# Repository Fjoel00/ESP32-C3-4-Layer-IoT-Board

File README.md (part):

# ESP32-C3 4-Layer IoT Multisensor Board 🚀

Nodo IoT embebido multisensor de **4 capas**, compacto y de bajo consumo, basado en el microcontrolador **Espressif ESP32-C3-WROOM-02** (arquitectura RISC-V a 160 MHz con conectividad Wi-Fi 4 y Bluetooth 5 LE). 

El diseño integra una solución completa de gestión de energía con carga de batería LiPo y conmutación automática (*Power-Path Management*), interfaz USB-C nativa con puente USB-UART CP2102N y auto-reset, almacenamiento masivo local dual (Flash SPI externa de 32 Mbit + ranura MicroSD), sensor ambiental de alta precisión (temperatura, presión y humedad), fototransistor de luz ambiental y micrófono electret con etapa de preamplificación activa ajustable.

Este proyecto ha sido concebido bajo estrictas pautas de diseño electrónico profesional, cumpliendo con restricciones de compatibilidad electromagnética (EMC), integridad de señal (SI) para pares diferenciales USB y buses de alta velocidad, optimización térmica y validación DFM (*Design for Manufacturability*) para fabricación seriada.

---

## Render 3D del Hardware y Documentación

* **Esquemático Completo:** [Ver / Descargar Esquemático en PDF](./ESP32-IoT-4-Layer-3D-Layout.pdf)
* **Visualización de PCB 3D:** [Ver / Descargar Vista 3D en PDF](./ESP32-IoT-4-Layer-3D-PCB.pdf)
* **Archivos Gerber y Taladros (NextPCB / HQ DFM):** [Descargar Paquete Gerber ZIP](./HQDMF/Gerber_ESP32-IoT-4-Layer.zip)

---

## Tabla de Contenidos
- [1. Descripción General del Proyecto](#1-descripción-general-del-proyecto)
- [2. Arquitectura de Hardware y Características Principales](#2-arquitectura-de-hardware-y-características-principales)
  - [2.1 Microcontrolador y Conectividad](#21-microcontrolador-y-conectividad)
  - [2.2 Gestión de Energía y Batería (Power-Path Management)](#22-gestión-de-energía-y-batería-power-path-management)
  - [2.3 Sensores Integrados](#23-sensores-integrados)
  - [2.4 Almacenamiento Local y Puntos de Prueba](#24-almacenamiento-local-y-puntos-de-prueba)
  - [2.5 Interfaz de Usuario y Cabezales de Expansión](#25-interfaz-de-usuario-y-cabezales-de-expansión)
- [3. Diseño de PCB y Stackup (4 Capas)](#3-diseño-de-pcb-y-stackup-4-capas)
  - [3.1 Distribución del Stackup y Dimensiones](#31-distribución-del-stackup-y-dimensiones)
  - [3.2 Enrutamiento de Señales Críticas y Pares Diferenciales USB](#32-enrutamiento-de-señales-críticas-y-pares-diferenciales-usb)
  - [3.3 Clases de Red (Net Classes) y Reglas de Diseño](#33-clases-de-red-net-classes-y-reglas-de-diseño)
  - [3.4 Consideraciones de RF y Planos de Cobre](#34-consideraciones-de-rf-y-planos-de-cobre)
- [4. Estructura del Repositorio y Hojas del Esquemático](#4-estructura-del-repositorio-y-hojas-del-esquemático)
- [5. Lista de Materiales (BOM Resumida)](#5-lista-de-materiales-bom-resumida)
- [6. Herramientas y Recursos Utilizados](#6-herramientas-y-recursos-utilizados)
- [7. Créditos y Referencias](#7-créditos-y-referencias)

---

## 1. Descripción General del Proyecto

La placa ha sido desarrollada como una plataforma integral de adquisición de datos en tiempo real y telemetría edge computing. Permite monitorear parámetros ambientales, acústicos y luminosos, procesarlos localmente en el núcleo RISC-V del microcontrolador y transmitirlos a la nube (AWS IoT Core, ThingsBoard, Home Assistant, servidores MQTT) mediante Wi-Fi o Bluetooth LE.

```mermaid
flowchart LR
    USB["Puerto USB-C\n(SS-52400-002)"] --> ESD["Protección ESD\n(USBLC6-2SC6)"]
    ESD --> CP["Puente USB-UART\n(CP2102N)"]
    CP --> AutoReset["Auto-Reset / Boot\n(2x BC817)"]
    AutoReset --> ESP["ESP32-C3-WROOM-02\n(RISC-V 160MHz)"]

    USB --> Fuse["Fusible PPTC 1.1A\n(0ZCH0110AF2E)"]
    Fuse --> MCP["Cargador LiPo + Power Path\n(MCP73871)"]
    BAT["Batería LiPo 3.7V\n(JST-PH 2-pin)"] <--> MCP
    MCP --> LDO["Regulador LDO 3.3V\n(LM1117-3.3)"]
    LDO --> ESP

    ESP <--> BME["Sensor BME280\n(I2C: Temp/Hum/Pres)"]
    ESP <--> TEMT["Sensor TEMT6000\n(ADC: Luz Ambiental)"]
    ESP <--> MIC["Micrófono + MAX4466\n(ADC: Acústica)"]
    ESP <--> Flash["Flash SPI 32 Mbit\n(W25Q32JV)"]
    ESP <--> SD["Ranura MicroSD\n(GSD090012SEU)"]
    ESP <--> EXP["Headers J4 / J5\n(GPIO & OLED I2C)"]
```

---

## 2. Arquitectura de Hardware y Características Principales

### 2.1 Microcontrolador y Conectividad
* **MCU:** Módulo **ESP32-C3-WROOM-02-H4** de Espressif Systems.
  * Núcleo: Procesador RISC-V de 32 bits y un solo núcleo a una frecuencia de hasta 160 MHz.
  * Memoria: 400 KB de SRAM interna, 384 KB de ROM y 4 MB de memoria Flash integrada en encapsulado SiP.
  * Conectividad RF: Subsistema Wi-Fi 802.11 b/g/n (hasta 150 Mbps) y Bluetooth 5 (LE) con antena PCB tipo MIFA integrada.
* **Interfaz USB-C:** Conector hembra reversible **SS-52400-002** (Bel Fuse) de 24 pines con resistencias de configuración de canal CC1/CC2 de 5.1 kΩ (`R3` y `R7`), garantizando compatibilidad con cargadores y puertos USB-C estándar (5 V @ hasta 3 A).
* **Supresión de Transitorios ESD:** Red de diodos de protección **USBLC6-2SC6** (`U2`, encapsulado SOT-23-6) de muy baja capacitancia parásita (<3.5 pF) para proteger las líneas `USB_DP`, `USB_DN` y el riel `VBUS` contra descargas electrostáticas de hasta ±15 kV por aire y ±8 kV por contacto (IEC 61000-4-2 nivel 4).
* **Puente USB a UART:** Circuito integrado **CP2102N-Axx-xQFN20** (`U3`, encapsulado QFN-20 de 3x3 mm) con soporte de velocidades de baudios de hasta 3 Mbaud.
  * Indicadores visuales de actividad de transmisión (`LED5` rojo para `TXT`) y recepción (`LED6` verde para `RXT`).
  * Resistencias de amortiguación en serie de 50 Ω (`R13` y `R17`) en las líneas UART para reducir reflexiones de alta frecuencia.
* **Circuito de Auto-Programación / Auto-Reset:** Implementado mediante dos transistores NPN discretos **BC817** (`Q2` y `Q3`) controlados por las señales `DTR` y `RTS` del CP2102N, permitiendo la conmutación automática entre modo normal y modo de descarga de firmware (control de líneas `EN` y `GPIO9/BOOT`) sin requerir pulsación manual de botones durante el flasheo desde el ESP-IDF o PlatformIO.

### 2.2 Gestión de Energía y Batería (Power-Path Management)
* **Controlador de Carga LiPo:** Circuito integrado **MCP73871-4CCI/ML** (`U1`, QFN-20 de 4x4 mm con pad térmico expuesto).
  * Algoritmo de carga completo en corriente constante / tensión constante (CC/CV) con corte a 4.20 V.
  * **Power-Path Management Automático:** Conmuta de forma transparente el riel del sistema entre la entrada de alimentación externa (USB de 5 V) y la batería LiPo. Si la corriente de carga y consumo supera el límite provisto por USB, la batería asiste automáticamente al riel del sistema sin reiniciar el microcontrolador.
  * Monitoreo térmico mediante red resistiva simulando termistor NTC (`Net-(U1-THERM)`).
* **Conexión de Batería:** Conector de montaje superficial **JST B2B-PH-SM4-TB** (`J2`) con paso de 2.0 mm para baterías de polímero de litio (LiPo) de una celda (1S, 3.7 V nominal).
* **Protección de Entrada:** Fusible rearmable de coeficiente de temperatura positivo polimérico (PPTC) **0ZCH0110AF2E** (`F1`, tamaño 1210), con corriente de mantenimiento ($I_H$) de 1.10 A y tensión nominal de 16 V, protegiendo el hardware ante sobrecorrientes en el bus USB.
* **Regulación a 3.3 V:** Regulador lineal LDO de bajo dropout **LM1117MPX-3.3/NOPB** (`VR1`, encapsulado SOT-223) capaz de suministrar hasta 800 mA con excelente rechazo al rizado (PSRR).
  * Red de filtrado con condensadores de tantalio de baja ESR **10 µF** (`C4`, `C5`, `C12`, `C13`, encapsulado EIA 3216 / KEMET T491A) y cerámicos multicapa (MLCC) de desacoplo de alta frecuencia de **0.1 µF** y **1 µF**.
* **LEDs de Diagnóstico y Estado:**
  * `LED1` (Rojo): Indicador de batería en proceso de carga (`/CHARGING`, pin `STAT1`).
  * `LED2` (Azul): Indicador de fuente de alimentación válida presente (`/CHARGING_POWER_GOOD`, pin `/PG`).
  * `LED3` (Verde): Indicador de ciclo de carga completado (`/CHARGED`, pin `STAT2`).
  * `LED4` (Rojo): Indicador de riel de alimentación principal activo (+3.3V Power Good).

### 2.3 Sensores Integrados
* **Sensor Ambiental Multivariable (U6 - BME280):**
  * Fabricante: Bosch Sensortec (encapsulado LGA-8 metálico de 2.5 x 2.5 mm).
  * Mide simultáneamente temperatura ambiente (precisión ±0.5 °C), humedad relativa (precisión ±3 %) y presión barométrica (precisión ±1 hPa, permitiendo cálculo de altitud barométrica).
  * Interfaz de comunicación: Bus I2C conectado a las líneas `SDA` (`GPIO4`) y `SCL` (`GPIO5`) del ESP32-C3, con resistencias pull-up de 4.7 kΩ (`R21` y `R24`).
* **Sensor de Luz Ambiental (Q1 - TEMT6000X01):**
  * Fabricante: Vishay Semiconductors (encapsulado SMD 1206 transparente).
  * Fototransistor NPN de silicio epitaxial planar con sensibilidad espectral adaptada a la respuesta fotópica del ojo humano (longitud de onda pico $\lambda_p = 570\text{ nm}$).
  * Configuración en emisor común con resistencia de carga a tierra, entregando una señal analógica proporcional a la iluminancia (Lux) hacia el canal ADC `PHOTO_C` (`GPIO1` / Pin 17 del ESP32-C3).
* **Sensor Acústico y Preamplificador de Micrófono (MK1 + U7):**
  * **Micrófono:** Transductor de condensador electret omnidireccional **CMC-5042PF-AC** (`MK1`, CUI Devices, 5.0 mm de diámetro) con rango de frecuencia de 100 Hz a 20 kHz y relación señal/ruido (SNR) >58 dB.
  * **Preamplificador:** Amplificador operacional **MAX4466EXK** (`U7`, Maxim Integrated / Analog Devices en encapsulado SC-70-5) con ancho de banda de 600 kHz y salida rail-to-rail.
  * Integra polarización activa para el micrófono, acoplamiento AC mediante condensadores de 1 µF y 10 nF (`C21`, `C22`), y red de realimentación para control de ganancia dinámica entregando la señal acondicionada `MIC_OUT` (`GPIO0` / Pin 4 del ESP32-C3) para detección de audio, decibelímetro o análisis FFT.

### 2.4 Almacenamiento Local y Puntos de Prueba
* **Memoria Flash SPI Externa (U4 - W25Q32JVSSIQ):**
  * Memoria NOR Flash serial de **32 Mbit (4 MByte)** en encapsulado SOIC-8 (208 mil).
  * Conectada al bus SPI compartido (`SCLK`, `MOSI_DI`, `MISO_DO`) con línea de selección dedicada `CS` (`GPIO10`).
  * Resistencias de amortiguación en serie de 50 Ω (`R18`, `R19`, `R20`) para evitar rebotes capacitivos e interferencias inductivas a altas frecuencias de reloj (hasta 133 MHz).
* **Ranura para Tarjeta MicroSD (J3 - GSD090012SEU):**
  * Conector push-push/push-pull de montaje superficial de Amphenol ICC.
  * Opera en modo SPI utilizando la línea de selección de chip dedicada `CS_SD` (`GPIO3`).
  * Permite registro continuo de datos (*datalogging*) masivo, almacenamiento de certificados criptográficos SSL/TLS, configuración JSON o recursos multimedia web locales.
* **Puntos de Prueba (Test Points):**
  * Cinco pads circulares de 1.0 mm de diámetro accesibles en la cara superior para conexión directa de analizadores lógicos o sondas de osciloscopio:
    * `TP1`: Bus SPI - MOSI
    * `TP2`: Bus SPI - MISO
    * `TP3`: Bus SPI - SCLK
    * `TP4`: Chip Select MicroSD (`CS_SD`)
    * `TP5`: Chip Select Flash SPI (`CS`)

### 2.5 Interfaz de Usuario y Cabezales de Expansión
* **Pulsadores Físicos de Perfil Bajo:**
  * `S1` (`BOOT`): Pulsador táctil SMD de precisión (`SW_USLPT2819DT2TR`, TE Connectivity) conectado a `GPIO9` con filtro capacitivo de 1 µF (`C20`) y resistencia pull-up de 10 kΩ (`R31`).
  * `S2` (`RESET`): Pulsador táctil idéntico conectado a la línea de habilitación `EN` con condensador de temporización de 0.1 µF (`C19`) y pull-up de 10 kΩ (`R30`).
* **Conector de Expansión I2C / Pantalla OLED (J5):**
  * Header hembra/macho estándar paso 2.54 mm de 4 pines con el pinout canónico para módulos display OLED SSD1306 (0.96 pulgada, 128x64 píxeles):
    * **Pin 1:** `+3.3V` (Alimentación regulada)
    * **Pin 2:** `SDA` (Línea de datos I2C)
    * **Pin 3:** `SCL` (Línea de reloj I2C)
    * **Pin 4:** `GND` (Referencia común de masa)
* **Conector de Expansión de GPIOs Multipropósito (J4):**
  * Header paso 2.54 mm de 5 pines para conectar actuadores externos, relés o periféricos SPI adicionales:
    * **Pin 1:** `+3.3V`
    * **Pin 2:** `GPIO8` (Línea digital de entrada/salida)
    * **Pin 3:** `GPIO18` (Línea digital de entrada/salida)
    * **Pin 4:** `GPIO19` (Línea digital de entrada/salida)
    * **Pin 5:** `GND`

---

## 3. Diseño de PCB y Stackup (4 Capas)

La placa utiliza una arquitectura multicapa de **4 estratos de cobre** con espesor final estándar de 1.6 mm y material dieléctrico FR-4 ($\varepsilon_r = 4.5, \tan\delta = 0.02$). La estrategia de capas prioriza la integridad de señal, la mitigación de emisiones radiadas (EMI) y una distribución eficiente de potencia.

### 3.1 Distribución del Stackup y Dimensiones
* **Dimensiones del Contorno (Edge Cuts):** 94.6 mm x 58.5 mm con esquinas redondeadas ($R = 2.0\text{ mm}$) y recorte perimetral para el módulo de RF.
* **Estructura Detallada de Capas:**

| Estrato | Nombre de Capa | Tipo | Espesor | Material | Función y Asignación de Señales |
| :---: | :--- | :--- | :---: | :---: | :--- |
| - | **F.SilkS / F.Mask** | Serigrafía / Solder Mask | 0.010 mm | Tinta epóxica | Identificación de componentes y máscara antisoldante blanca/verde |
| **L1** | **F.Cu (Top)** | Cobre (1 oz) | 0.035 mm | Cobre | **Componentes SMD + Enrutamiento de señales críticas**, par diferencial USB 2.0, pistas de RF, buses SPI/I2C y vertidos de cobre poligonales locales (+5V, VBAT, VBUS, GND). |
| - | **Dielectric 1** | Prepreg (FR-4) | **0.100 mm** | Prepreg 1080/2116 | Aislamiento dieléctrico delgado ($\varepsilon_r = 4.5$) optimizado para acoplamiento estrecho con L2 y control de impedancia microstrip. |
| **L2** | **In1.Cu (Inner 1)** | Cobre (1 oz) | 0.035 mm | Cobre | **Plano continuo de GND (Referencia de Retorno):** Proporciona un plano de masa uniforme debajo de todas las pistas de señal de alta velocidad de L1, minimizando el bucle de corriente de retorno y suprimiendo la diafonía (*crosstalk*). *(En combinación con planos de alimentación divididos/coplanares)*. |
| - | **Dielectric 2** | Core (FR-4) | **1.240 mm** | Núcleo FR-4 | Dieléctrico rígido central aislante que otorga estabilidad mecánica al circuito impreso. |
| **L3** | **In2.Cu (Inner 2)** | Cobre (1 oz) | 0.035 mm | Cobre | **Planos de Alimentación Divididos (Power Planes):** Distribución de potencia mallada y vertida en polígonos para rieles `+3.3V`, `+5V_USB` y `/VBUS`, garantizando baja impedancia de distribución (PDN) hacia los circuitos integrados. |
| - | **Dielectric 3** | Prepreg (FR-4) | **0.100 mm** | Prepreg 1080/2116 | Aislamiento dieléctrico simétrico respecto a L1. |
| **L4** | **B.Cu (Bottom)** | Cobre (1 oz) | 0.035 mm | Cobre | **Enrutamiento de señales secundarias** de control y vertido continuo de cobre de retorno GND con aislamiento perimetral. |
| - | **B.Mask / B.SilkS** | Solder Mask / Serigrafía | 0.010 mm | Tinta epóxica | Máscara antisoldante inferior y marcas de fabricación |
| **Total** | **Grosor Nominal** | **PCB Completa** | **~1.60 mm** | FR-4 / Cu | Tolerancia estándar de manufactura IPC-Class 2 |

### 3.2 Enrutamiento de Señales Críticas y Pares Diferenciales USB
* **Par Diferencial USB 2.0 (`USB_DP` / `USB_DN`):**
  * Impedancia diferencial objetivo: $Z_{diff} = 90\ \Omega \pm 10\%$.
  * Ancho de pista (*Track Width*): $0.20\text{ mm}$ (8 mil).
  * Separación intra-par (*Diff Pair Gap*): $0.20\text{ mm}$ (8 mil).
  * Distancia al plano de masa subyacente (L1 a L2): $0.10\text{ mm}$.
  * Enrutamiento acoplado de extremo a extremo, sin quiebres a 90° (curvas redondeadas en 45° o con radio de acuerdo), evitando cruces de planos de referencia fracturados y minimizando vías de transición.
  * Respeto estricto de la regla 3W respecto a otras señales de reloj y analógicas.
* **Bus Serial SPI (Clock @ 40–80 MHz):**
  * Pistas `SCLK`, `MOSI` y `MISO` enrutadas con ancho de $0.30\text{ mm}$ y separación mínima de $0.20\text{ mm}$.
  * Resistencias de terminación en serie amortiguadoras ($50\ \Omega$) colocadas en proximidad inmediata al pin emisor para amortiguar sobreimpulsos (*ringing*).

### 3.3 Clases de Red (Net Classes) y Reglas de Diseño

Para asegurar la repetibilidad y el aislamiento eléctrico, se configuraron clases de red específicas en KiCad:

| Clase de Red | Redes Asignadas | Ancho de Pista | Aislamiento (Clearance) | Diámetro Vía | Taladro Vía |
| :--- | :--- | :---: | :---: | :---: | :---: |
| **Default** | Señales lógicas generales | 0.25 mm | 0.20 mm | 0.60 mm | 0.30 mm |
| **USB_data** | `*USB_D?`, `*RX*` (USB 2.0 D+/D-) | 0.25 mm *(Diff: 0.20 mm)* | 0.15 mm *(Gap: 0.20 mm)* | 0.50 mm | 0.30 mm |
| **3.3V** | `+3.3V` (Riel principal regulado) | 0.50 mm | 0.20 mm | 0.60 mm | 0.40 mm |
| **5V_USB** | `+5*`, `+5V*` | 0.25 mm | 0.20 mm | 0.60 mm | 0.30 mm |
| **VBUS** | `*VBUS`, `*VBAT` (Alimentación primaria) | 0.60 mm | 0.15 mm | 0.60 mm | 0.30 mm |
| **GND** | `GND` (Red de retorno principal) | 0.50 mm | 0.20 mm | 0.60 mm | 0.40 mm |
| **SPI** | `*MISO*`, `*MOSI*`, `*SCLK*`, `*CS*` | 0.30 mm | 0.15 mm | 0.50 mm | 0.30 mm |
| **I2C** | `*SDA*`, `*SCL*` | 0.30 mm | 0.15 mm | 0.50 mm | 0.30 mm |
| **control** | `*RTS*`, `*BOOT*`, `*EN` | 0.25 mm | 0.15 mm | 0.50 mm | 0.30 mm |
| **GPIO** | `*GPIO?`, `*GPIO??` | 0.25 mm | 0.15 mm | 0.50 mm | 0.30 mm |
| **sensor_data**| `*PHOTO_C`, `*MIC_OUT` (Analógicas) | 0.25 mm | 0.15 mm | 0.50 mm | 0.30 mm |

### 3.4 Consideraciones de RF y Planos de Cobre
* **Zona de Exclusión de Antena (*RF Keepout Zone*):** El módulo ESP32-C3-WROOM-02 cuenta con una antena tipo Meandered Inverted-F Antenna (MIFA). Debajo de la sección de la antena y en una franja de extensión perimetral de al menos 15 mm se definieron zonas de exclusión absolutas (*Keepouts*) sin vertidos de cobre, sin pistas y sin vías en ninguna de las 4 capas (`F.Cu`, `In1.Cu`, `In2.Cu`, `B.Cu`), permitiendo la radiación electromagnética omnidireccional sin atenuación ni desadaptación de impedancias de la antena (50 Ω).
* **Alivio Térmico (*Thermal Reliefs*):** Todas las conexiones a planos masivos de cobre cuentan con radios térmicos de 4 rayos para garantizar una soldabilidad óptima durante el reflujo y retrabajo manual sin disipación prematura del calor.

---

## 4. Estructura del Repositorio y Hojas del Esquemático

El proyecto sigue una arquitectura de esquemáticos jerárquicos de 4 hojas en KiCad, separando lógicamente los dominios de potencia, microcontrolador, sensórica e interacción humana:

```mermaid
graph TD
    Root["Hoja 1 (Raíz): ESP32-IoT-4-Layer.kicad_sch\n• Conector USB-C & Fusible PPTC\n• Cargador LiPo MCP73871 con Power-Path\n• Regulador LDO LM1117-3.3V\n• LEDs de Estado de Carga y Power"]
    
    Sub1["Hoja 2: esp32-c3-02.kicad_sch\n• MCU ESP32-C3-WROOM-02\n• Puente USB-UART CP2102N & ESD\n• Memoria NOR Flash SPI (W25Q32JV)\n• Ranura MicroSD (GSD090012SEU)\n• Puntos de Prueba SPI (TP1-TP5)"]
    
    Sub2["Hoja 3: sensors.kicad_sch\n• Sensor Ambiental BME280 (I2C)\n• Fototransistor TEMT6000 (Luz)\n• Micrófono CMC-5042PF-AC\n• Preamp MAX4466 con Bias Activo"]
    
    Sub3["Hoja 4: user_interface.kicad_sch\n• Pulsadores BOOT y RESET\n• Circuito Auto-Reset (Transistores BC817)\n• Header I2C / OLED Display (J5)\n• Header de Expansión GPIO (J4)"]

    Root --> Sub1
    Sub1 --> Sub2
    Sub1 --> Sub3
```

### Organización de Archivos en el Repositorio

```text
ESP32-IoT-4-Layer/
├── ESP32-IoT-4-Layer.kicad_pro       # Archivo principal del proyecto KiCad 9
├── ESP32-IoT-4-Layer.kicad_sch       # Hoja 1: Esquemático Raíz (Gestión de Energía y USB-C)
├── esp32-c3-02.kicad_sch             # Hoja 2: Esquemático MCU ESP32-C3, CP2102N, Flash & SD
├── sensors.kicad_sch                 # Hoja 3: Esquemático Sensores (BME280, TEMT6000, Mic)
├── user_interface.kicad_sch          # Hoja 4: Esquemático UI, Pulsadores, Auto-Reset y Headers
├── ESP32-IoT-4-Layer.kicad_pcb       # Archivo de diseño de circuito impreso (Layout 4 capas)
├── ESP32-IoT-4-Layer.kicad_prl       # Archivo de reglas locales de diseño KiCad
├── fp-lib-table                      # Tabla de librerías locales de footprints
├── sym-lib-table                     # Tabla de librerías locales de símbolos esquemáticos
│
├── Datasheets/                       # Hojas de datos técnicas de componentes principales
│   ├── esp32-c3-wroom-02_datasheet_en.pdf
│   ├── MCP73871-4CCIML-datasheet.pdf
│   ├── BME280_Bosch.pdf
│   ├── TEMT6000X01_Vishay_Semiconductor.pdf
│   ├── CMC-5042PF-AC_CUI_Devices.pdf
│   ├── W25Q32JVSSIQ_Winbond.pdf
│   ├── gsd09001xseu.pdf
│   └── lm1117.pdf
│
├── HQDMF/                            # Paquete de fabricación validado para fábrica (NextPCB)
│   ├── Gerber_ESP32-IoT-4-Layer.zip  # Archivo comprimido listo para cotización en fábrica
│   └── Gerber_ESP32-IoT-4-Layer/     # Archivos Gerber RS-274X y Drill NC individuales
│       ├── ESP32-IoT-4-Layer-CuTop.gbr
│       ├── ESP32-IoT-4-Layer-CuIn1.gbr
│       ├── ESP32-IoT-4-Layer-CuIn2.gbr
│       ├── ESP32-IoT-4-Layer-CuBottom.gbr
│       ├── ESP32-IoT-4-Layer-EdgeCuts.gbr
│       ├── ESP32-IoT-4-Layer-PTH.drl
│       └── ESP32-IoT-4-Layer-NPTH.drl
│
├── Librerias/                        # Librerías locales de componentes del proyecto
│   ├── Symbols/                      # Símbolos esquemáticos (.kicad_sym)
│   ├── Footprints/                   # Huellas PCB (.kicad_mod)
│   └── Models3D/                     # Modelos tridimensionales mecánicos (.step)
│
├── ESP32-IoT-4-Layer-3D-Model.png    # Render 3D de alta resolución (Vista superior frontal)
├── ESP32-IoT-4-Layer-3D-Model-1.png  # Render 3D alternativo (Vista en perspectiva)
├── ESP32-IoT-4-Layer-PCB-Layout.png  # Captura del enrutamiento multicapa de la PCB
├── ESP32-IoT-4-Layer-3D-PCB.pdf     # Documento técnico de inspección 3D
├── ESP32-IoT-4-Layer-3D-Layout.pdf  # Documento técnico de cotas y layout
└── README.md                         # Documentación técnica del proyecto
```

---

## 5. Lista de Materiales (BOM Resumida)

| Referencia | Cant. | Componente / Valor | Encapsulado | Fabricante / N° de Pieza | Función en el Circuito |
| :--- | :---: | :--- | :--- | :--- | :--- |
| **U5** | 1 | ESP32-C3-WROOM-02-H4 | Módulo SMD | Espressif Systems | Microcontrolador RISC-V 160MHz con Wi-Fi/BLE |
| **U1** | 1 | MCP73871-4CCI/ML | QFN-20 (4x4mm) | Microchip Technology | Cargador LiPo con Power-Path Management |
| **VR1** | 1 | LM1117MPX-3.3/NOPB | SOT-223 | Texas Instruments / onsemi | Regulador de tensión lineal LDO 3.3V 800mA |
| **U3** | 1 | CP2102N-Axx-xQFN20 | QFN-20 (3x3mm) | Silicon Labs | Puente convertidor USB a UART |
| **U2** | 1 | USBLC6-2SC6 | SOT-23-6 | STMicroelectronics | Matriz de diodos de supresión ESD para USB 2.0 |
| **U4** | 1 | W25Q32JVSSIQ | SOIC-8 (208 mil) | Winbond Electronics | Memoria NOR Flash SPI externa de 32 Mbit |
| **U6** | 1 | BME280 | LGA-8 (2.5x2.5mm)| Bosch Sensortec | Sensor I2C de Temp, Humedad y Presión |
| **Q1** | 1 | TEMT6000X01 | SMD 1206 | Vishay Semiconductors | Sensor fototransistor de luz ambiental (Lux) |
| **MK1** | 1 | CMC-5042PF-AC | SMD Diam. 5mm | CUI Devices | Micrófono de condensador electret omnidireccional |
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
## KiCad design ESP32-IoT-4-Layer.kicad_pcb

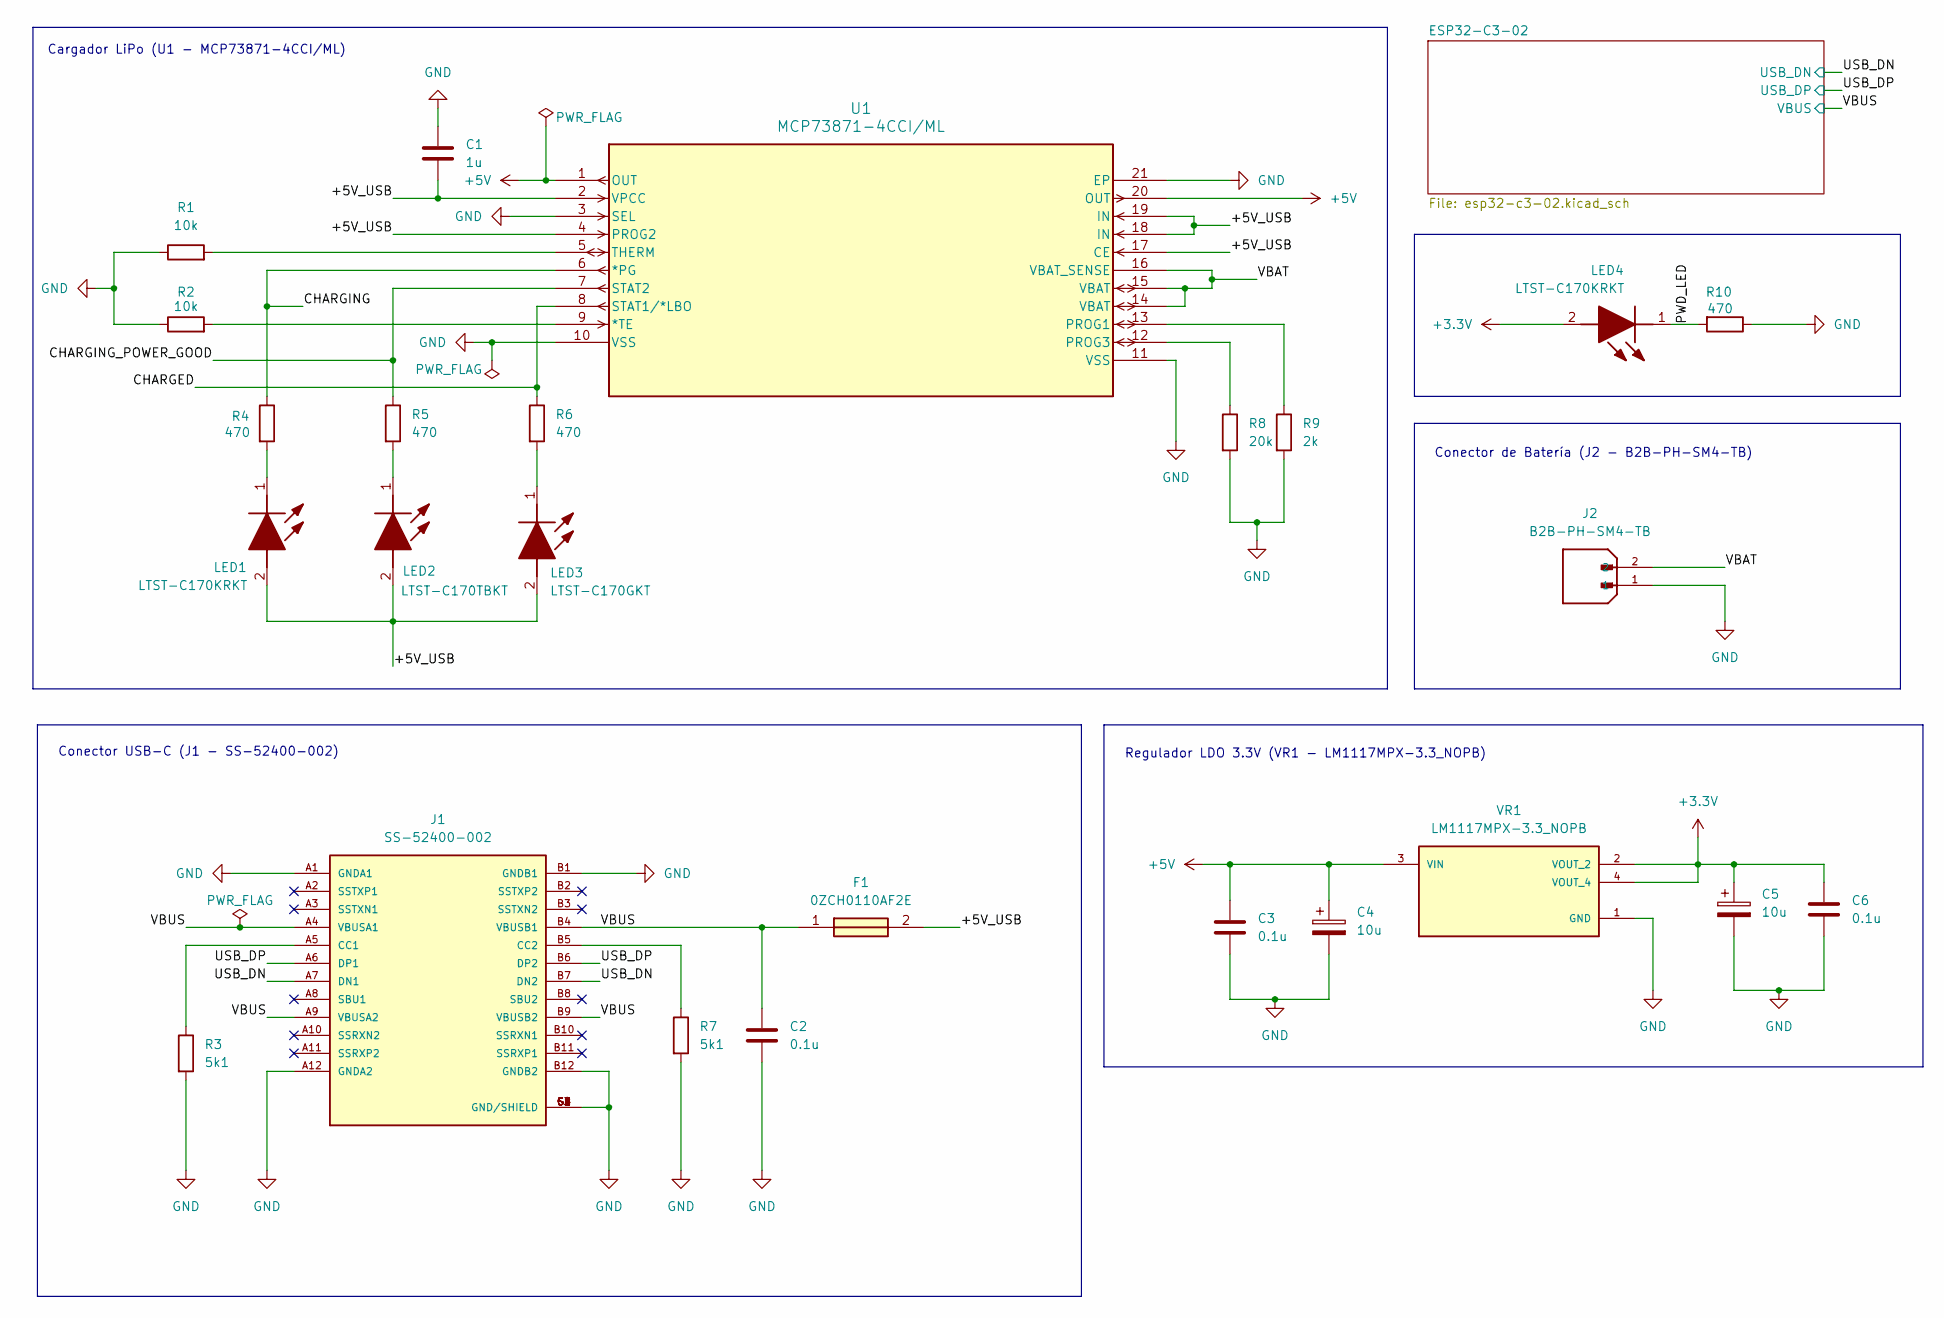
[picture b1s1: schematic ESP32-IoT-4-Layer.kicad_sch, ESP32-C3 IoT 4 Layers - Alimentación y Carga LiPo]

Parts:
C1: 1u; C_0805_2012Metric
C2, C3, C6: 0.1u; C_0805_2012Metric
C4, C5: 10u; T491A
F1: 0ZCH0110AF2E; FUSC3226X100N; Manufacturer_Part_Number 0ZCH0110AF2E
J1: SS-52400-002; BELFUSE_SS-52400-002; PARTREV A0
J2: B2B-PH-SM4-TB; JST_B2B-PH-SM4-TB; PARTREV N/A
LED1, LED4: LTST-C170KRKT; LEDC2012X120N; Manufacturer_Part_Number LTST-C170KRKT; Mouser Part Number 859-LTST-C170KRKT
LED2: LTST-C170TBKT; LEDC2012X120N; Manufacturer_Part_Number LTST-C170TBKT; Mouser Part Number 859-LTST-C170TBKT
LED3: LTST-C170GKT; LEDC2012X120N; Manufacturer_Part_Number LTST-C170GKT; Mouser Part Number 859-LTST-C170GKT
R1, R2: 10k; R_0805_2012Metric
R3, R7: 5k1; R_0805_2012Metric
R4, R5, R6, R10: 470; R_0805_2012Metric
R8: 20k; R_0805_2012Metric
R9: 2k; R_0805_2012Metric
U1: MCP73871-4CCI/ML; QFN50P400X400X100-21N
VR1: LM1117MPX-3.3_NOPB; VREG_LM1117MPX-3.3; PARTREV O

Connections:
+3.3V: C5.1, C6.1, LED4.2 (A), VR1.2 (VOUT_2), VR1.4 (VOUT_4); also elsewhere on the board
+5V: C3.1, C4.1, U1.1 (OUT), U1.20 (OUT), VR1.3 (VIN)
/+5V_USB: C1.2, F1.2, LED1.2 (A), LED2.2 (A), LED3.2 (A), U1.2 (VPCC), U1.4 (PROG2), U1.17 (CE), U1.18 (IN), U1.19 (IN)
/CHARGED: R6.1, U1.8 (STAT1/*LBO)
/CHARGING: R4.1, U1.6 (*PG)
/CHARGING_POWER_GOOD: R5.1, U1.7 (STAT2)
/PWD_LED: LED4.1 (K), R10.2
/USB_DN: J1.A7 (DN1), J1.B7 (DN2); also elsewhere on the board
/USB_DP: J1.A6 (DP1), J1.B6 (DP2); also elsewhere on the board
/VBAT: J2.2, U1.14 (VBAT), U1.15 (VBAT), U1.16 (VBAT_SENSE)
/VBUS: C2.1, F1.1, J1.A4 (VBUSA1), J1.A9 (VBUSA2), J1.B4 (VBUSB1), J1.B9 (VBUSB2); also elsewhere on the board
GND: C1.1, C2.2, C3.2, C4.2, C5.2, C6.2, J1.A1 (GNDA1), J1.A12 (GNDA2), J1.B1 (GNDB1), J1.B12 (GNDB2), J1.G1 (GND/SHIELD), J1.G2 (GND/SHIELD), J1.G3 (GND/SHIELD), J1.G4 (GND/SHIELD), J1.S1 (GND/SHIELD), J1.S2 (GND/SHIELD), J1.S3 (GND/SHIELD), J1.S4 (GND/SHIELD), J2.1, R1.1, R2.1, R3.2, R7.2, R8.2, R9.2, R10.1, U1.3 (SEL), U1.10 (VSS), U1.11 (VSS), U1.21 (EP), VR1.1 (GND); also elsewhere on the board
unnamed: J1.A5 (CC1), R3.1
unnamed: J1.B5 (CC2), R7.1
unnamed: LED1.1 (K), R4.2
unnamed: LED2.1 (K), R5.2
unnamed: LED3.1 (K), R6.2
unnamed: R2.2, U1.9 (*TE)
unnamed: R9.1, U1.13 (PROG1)
unnamed: R8.1, U1.12 (PROG3)
unnamed: R1.2, U1.5 (THERM)

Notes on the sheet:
Conector USB-C (J1 - SS-52400-002)
Cargador LiPo (U1 - MCP73871-4CCI/ML)
Regulador LDO 3.3V (VR1 - LM1117MPX-3.3_NOPB)
Conector de Batería (J2 - B2B-PH-SM4-TB)

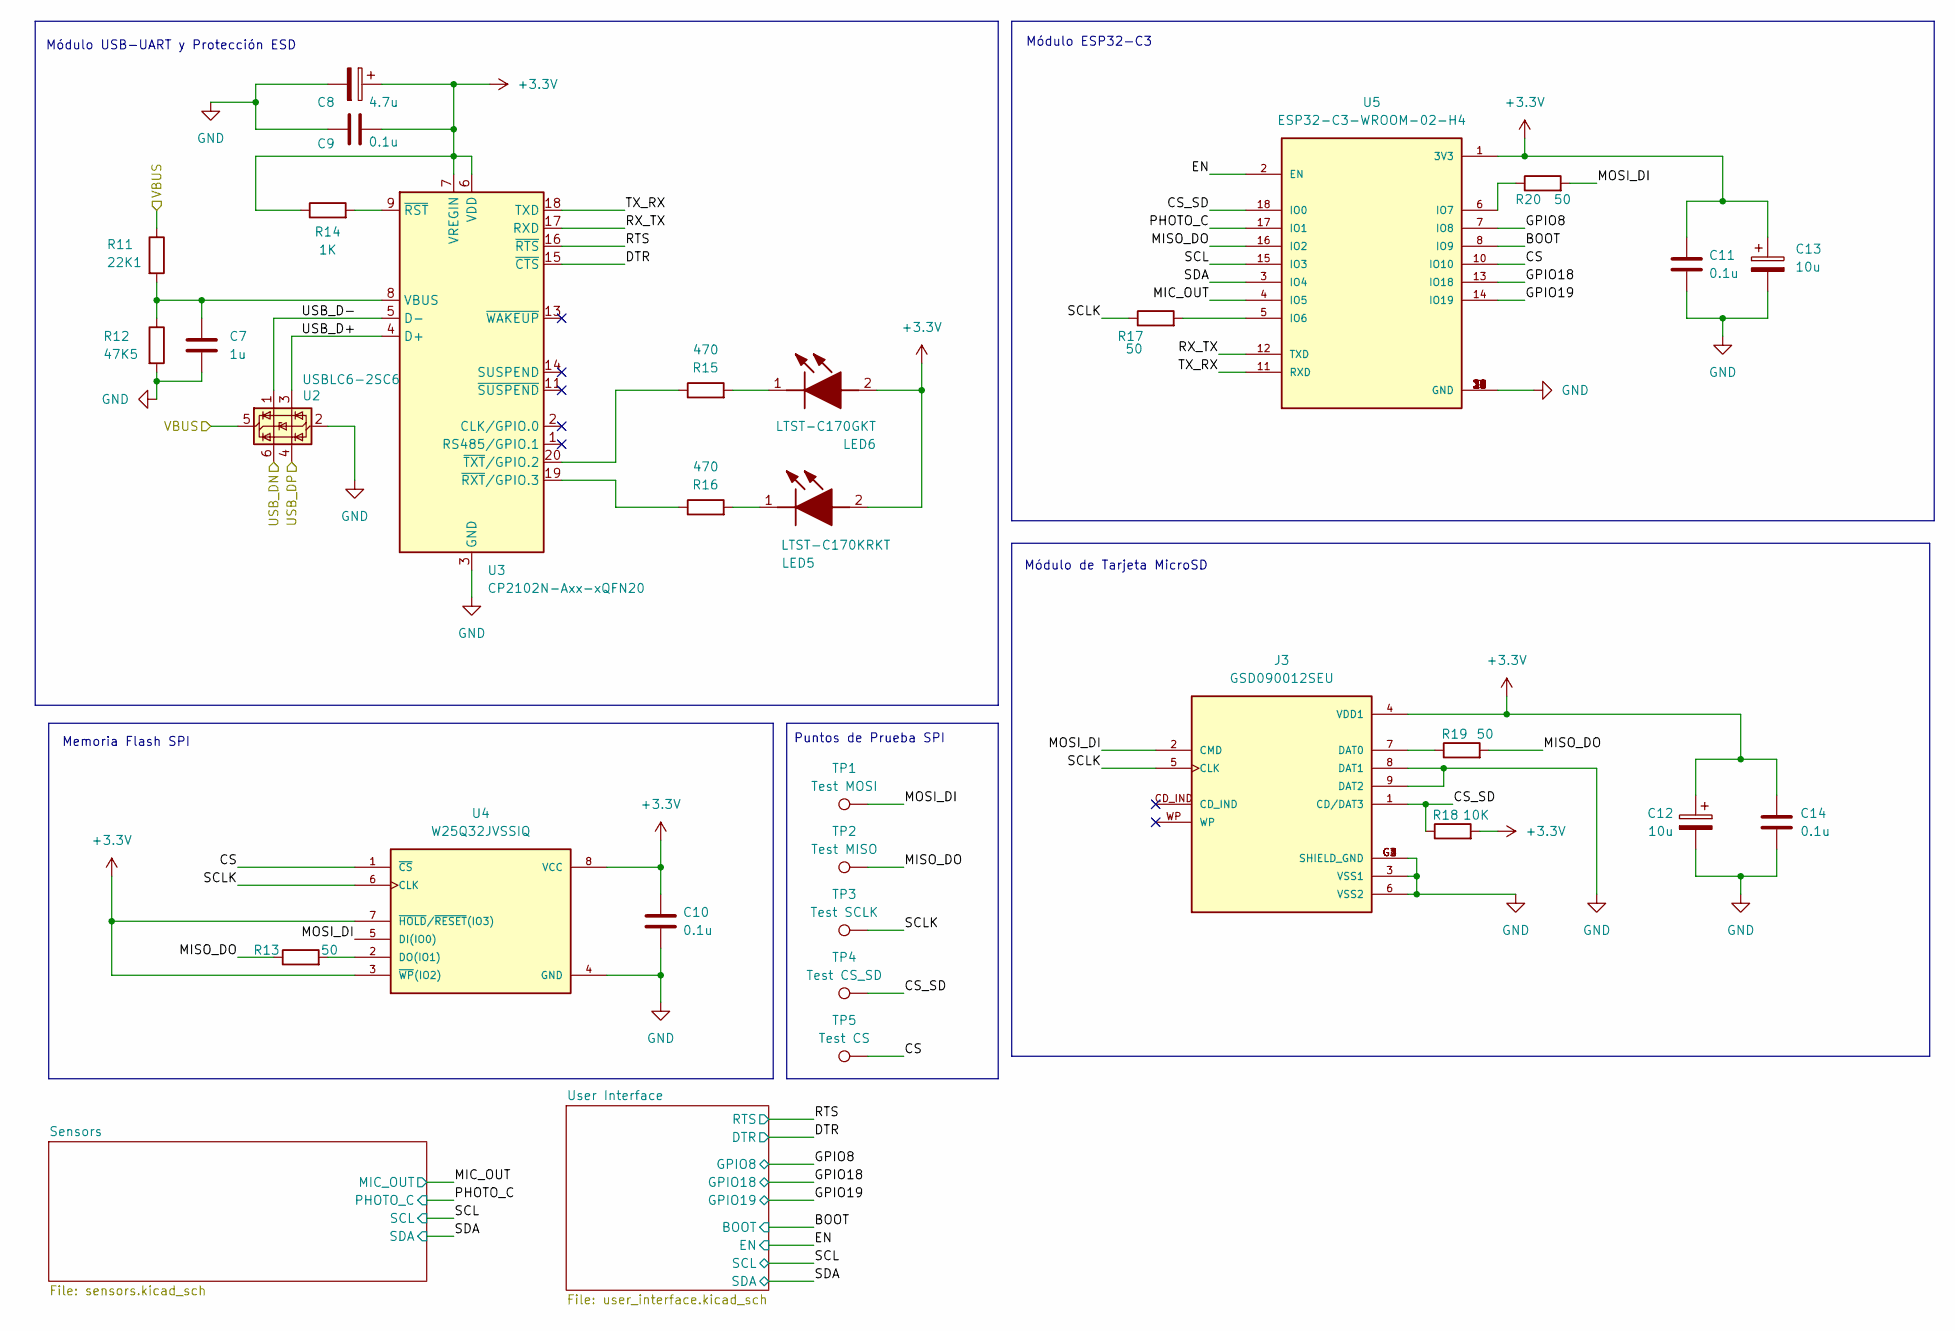
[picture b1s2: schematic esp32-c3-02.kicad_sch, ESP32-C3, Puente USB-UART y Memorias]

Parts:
C7: 1u; C_0805_2012Metric
C8: 4.7u; T491A
C9, C10, C11, C14: 0.1u; C_0805_2012Metric
C12, C13: 10u; T491A
J3: GSD090012SEU; AMPHENOL_GSD090012SEU; PARTREV E
LED5: LTST-C170KRKT; LEDC2012X120N; Manufacturer_Part_Number LTST-C170KRKT; Mouser Part Number 859-LTST-C170KRKT
LED6: LTST-C170GKT; LEDC2012X120N; Manufacturer_Part_Number LTST-C170GKT; Mouser Part Number 859-LTST-C170GKT
R11: 22K1; R_0805_2012Metric
R12: 47K5; R_0805_2012Metric
R13, R17, R19, R20: 50; R_0805_2012Metric
R14: 1K; R_0805_2012Metric
R15, R16: 470; R_0805_2012Metric
R18: 10K; R_0805_2012Metric
TP1: Test MOSI; TestPoint_Pad_D1.0mm
TP2: Test MISO; TestPoint_Pad_D1.0mm
TP3: Test SCLK; TestPoint_Pad_D1.0mm
TP4: Test CS_SD; TestPoint_Pad_D1.0mm
TP5: Test CS; TestPoint_Pad_D1.0mm
U2: USBLC6-2SC6; SOT-23-6
U3: CP2102N-Axx-xQFN20; SiliconLabs_QFN-20-1EP_3x3mm_P0.5mm_EP1.8x1.8mm
U4: W25Q32JVSSIQ; SOIC127P790X216-8N; M_PART_NUMBER W25QXX
U5: ESP32-C3-WROOM-02-H4; MODULE_ESP32-C3-WROOM-02-H4

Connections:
+3.3V: C8.1, C9.2, C10.1, C11.1, C12.1, C13.1, C14.1, J3.4 (VDD1), LED5.2 (A), LED6.2 (A), R14.1, R18.2, U3.6 (VDD), U3.7 (VREGIN), U4.3 (~WP(IO2)), U4.7 (~HOLD/~RESET(IO3)), U4.8 (VCC), U5.1 (3V3); also elsewhere on the board
/ESP32-C3-02/BOOT: U5.8 (IO9); also elsewhere on the board
/ESP32-C3-02/CS: TP5.1, U4.1 (~CS), U5.10 (IO10)
/ESP32-C3-02/CS_SD: J3.1 (CD/DAT3), R18.1, TP4.1, U5.18 (IO0)
/ESP32-C3-02/DTR: U3.15 (~CTS); also elsewhere on the board
/ESP32-C3-02/EN: U5.2 (EN); also elsewhere on the board
/ESP32-C3-02/GPIO8: U5.7 (IO8); also elsewhere on the board
/ESP32-C3-02/GPIO18: U5.13 (IO18); also elsewhere on the board
/ESP32-C3-02/GPIO19: U5.14 (IO19); also elsewhere on the board
/ESP32-C3-02/MIC_OUT: U5.4 (IO5); also elsewhere on the board
/ESP32-C3-02/MISO_DO: R13.1, R19.2, TP2.1, U5.16 (IO2)
/ESP32-C3-02/MOSI_DI: J3.2 (CMD), R20.2, TP1.1, U4.5 (DI(IO0))
/ESP32-C3-02/PHOTO_C: U5.17 (IO1); also elsewhere on the board
/ESP32-C3-02/RTS: U3.16 (~RTS); also elsewhere on the board
/ESP32-C3-02/RX_TX: U3.17 (RXD), U5.12 (TXD)
/ESP32-C3-02/SCL: U5.15 (IO3); also elsewhere on the board
/ESP32-C3-02/SCLK: J3.5 (CLK), R17.1, TP3.1, U4.6 (CLK)
/ESP32-C3-02/SDA: U5.3 (IO4); also elsewhere on the board
/ESP32-C3-02/TX_RX: U3.18 (TXD), U5.11 (RXD)
/ESP32-C3-02/USB_D+: U2.3 (I/O2), U3.4 (D+)
/ESP32-C3-02/USB_D-: U2.1 (I/O1), U3.5 (D-)
/USB_DN: U2.6 (I/O1); also elsewhere on the board
/USB_DP: U2.4 (I/O2); also elsewhere on the board
/VBUS: R11.1, U2.5 (VBUS); also elsewhere on the board
GND: C7.2, C8.2, C9.1, C10.2, C11.2, C12.2, C13.2, C14.2, J3.3 (VSS1), J3.6 (VSS2), J3.8 (DAT1), J3.9 (DAT2), J3.G1 (SHIELD_GND), J3.G2 (SHIELD_GND), J3.G3 (SHIELD_GND), J3.G4 (SHIELD_GND), R12.2, U2.2 (GND), U3.3 (GND), U3.12 (GND), U3.21 (GND), U4.4 (GND), U5.9 (GND), U5.19 (GND), U5.20 (GND), U5.21 (GND), U5.22 (GND), U5.23 (GND), U5.24 (GND), U5.25 (GND), U5.26 (GND), U5.27 (GND), U5.28 (GND), U5.29 (GND), U5.30 (GND), U5.31 (GND), U5.32 (GND), U5.33 (GND), U5.34 (GND), U5.35 (GND), U5.36 (GND), U5.37 (GND), U5.38 (GND), U5.39 (GND); also elsewhere on the board
unnamed: J3.7 (DAT0), R19.1
unnamed: LED5.1 (K), R16.2
unnamed: LED6.1 (K), R15.2
unnamed: C7.1, R11.2, R12.1, U3.8 (VBUS)
unnamed: R14.2, U3.9 (~RST)
unnamed: R16.1, U3.19 (~RXT/GPIO.3)
unnamed: R15.1, U3.20 (~TXT/GPIO.2)
unnamed: R13.2, U4.2 (DO(IO1))
unnamed: R17.2, U5.5 (IO6)
unnamed: R20.1, U5.6 (IO7)

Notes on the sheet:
Módulo de Tarjeta MicroSD
Módulo ESP32-C3
Memoria Flash SPI
Puntos de Prueba SPI
Módulo USB-UART y Protección ESD

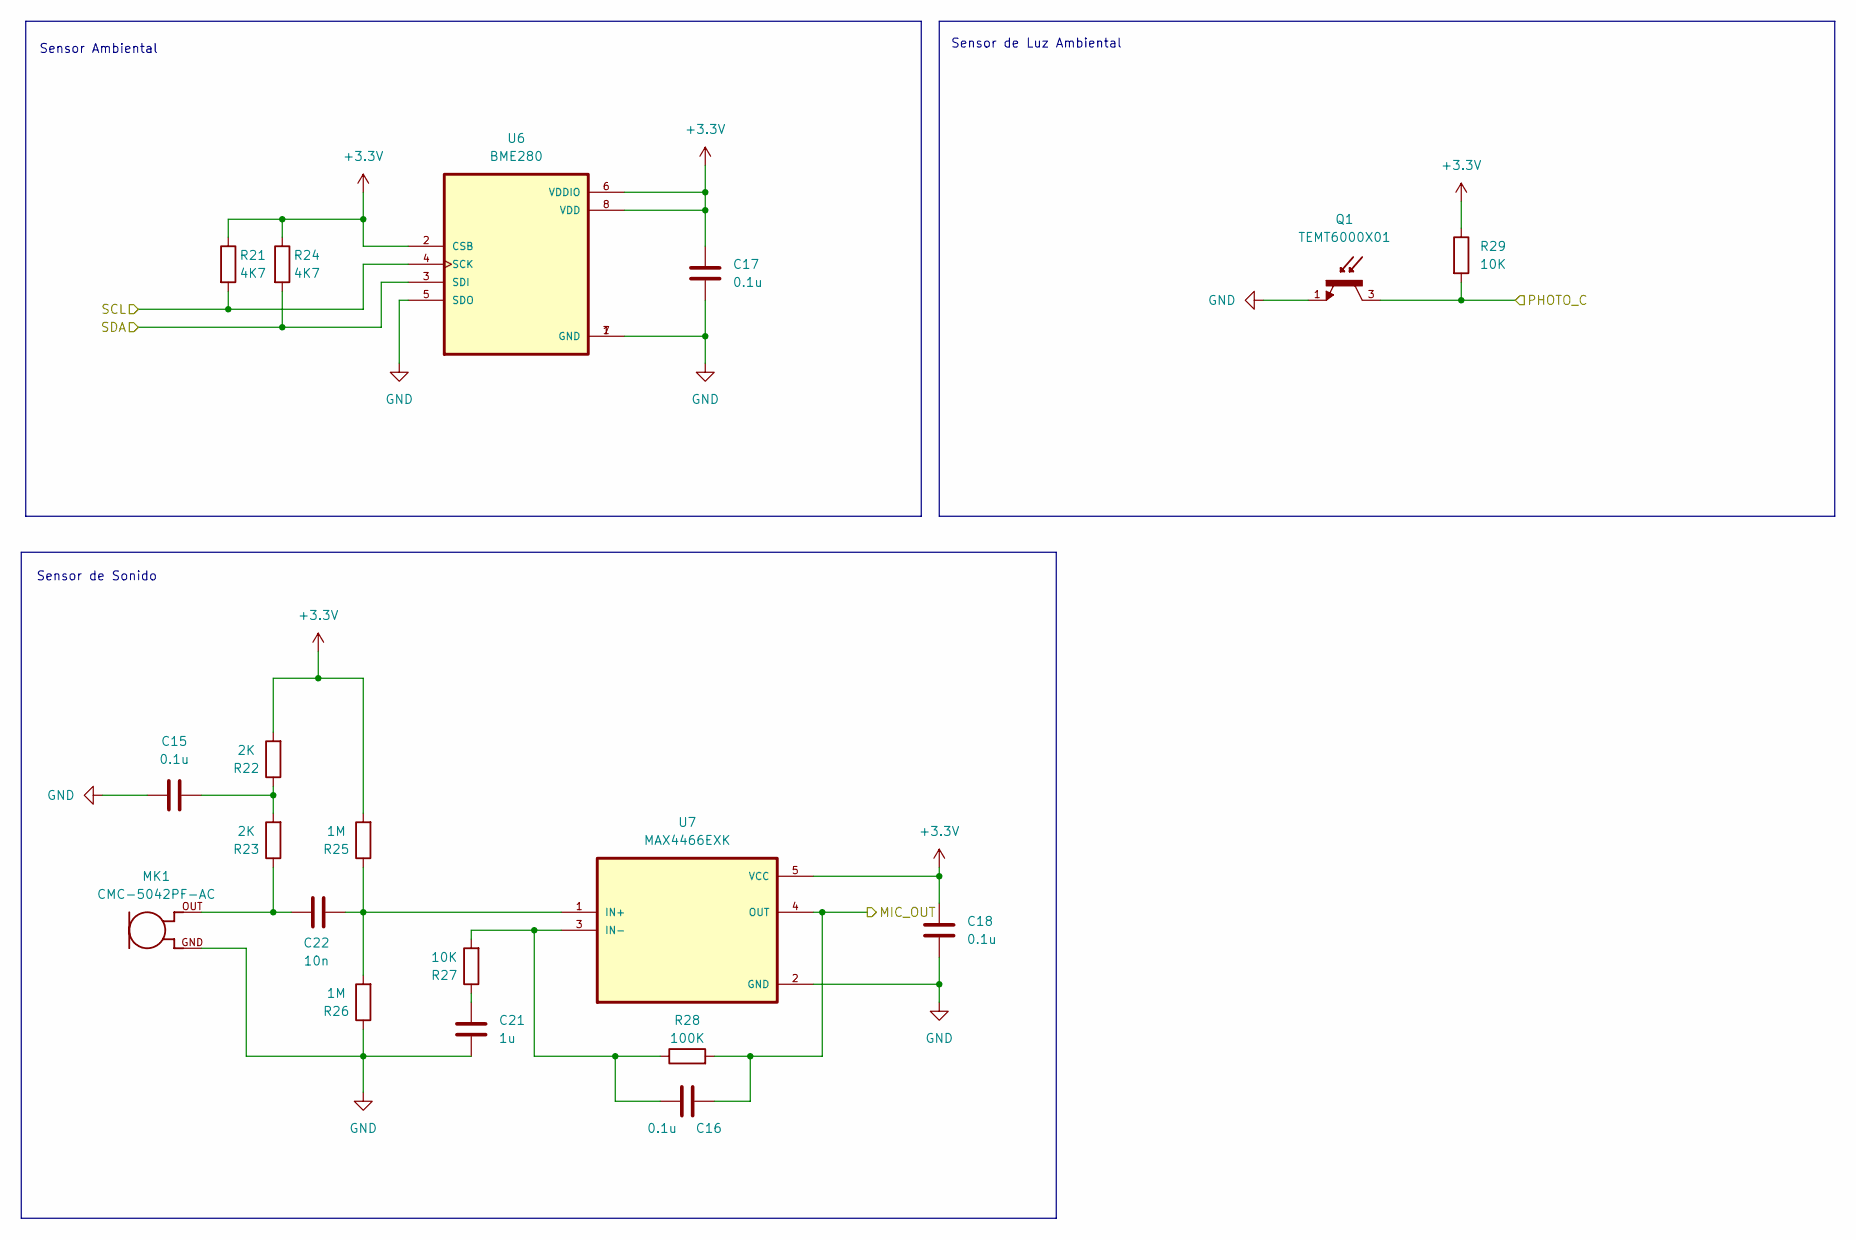
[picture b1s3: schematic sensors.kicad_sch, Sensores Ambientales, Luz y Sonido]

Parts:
C15, C16, C17, C18: 0.1u; C_0805_2012Metric
C21: 1u; C_0805_2012Metric
C22: 10n; C_0805_2012Metric
MK1: CMC-5042PF-AC; CUI_CMC-5042PF-AC
Q1: TEMT6000X01; TRANS_TEMT6000X01; PARTREV 1.9
R21, R24: 4K7; R_0805_2012Metric
R22, R23: 2K; R_0805_2012Metric
R25, R26: 1M; R_0805_2012Metric
R27, R29: 10K; R_0805_2012Metric
R28: 100K; R_0805_2012Metric
U6: BME280; PSON65P250X250X100-8N
U7: MAX4466EXK; SOT65P210X110-5N

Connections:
+3.3V: C17.1, C18.1, R21.1, R22.2, R24.1, R25.2, R29.1, U6.2 (CSB), U6.6 (VDDIO), U6.8 (VDD), U7.5 (VCC); also elsewhere on the board
/ESP32-C3-02/MIC_OUT: C16.1, R28.2, U7.4 (OUT); also elsewhere on the board
/ESP32-C3-02/PHOTO_C: Q1.3, R29.2; also elsewhere on the board
/ESP32-C3-02/SCL: R21.2, U6.4 (SCK); also elsewhere on the board
/ESP32-C3-02/SDA: R24.2, U6.3 (SDI); also elsewhere on the board
GND: C15.1, C17.2, C18.2, C21.1, MK1.GND, Q1.1, R26.1, U6.1 (GND), U6.5 (SDO), U6.7 (GND), U7.2 (GND); also elsewhere on the board
unnamed: C15.2, R22.1, R23.2
unnamed: C21.2, R27.1
unnamed: C22.1, MK1.OUT, R23.1
unnamed: C22.2, R25.1, R26.2, U7.1 (IN+)
unnamed: C16.2, R27.2, R28.1, U7.3 (IN-)

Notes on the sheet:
Sensor de Luz Ambiental
Sensor Ambiental
Sensor de Sonido

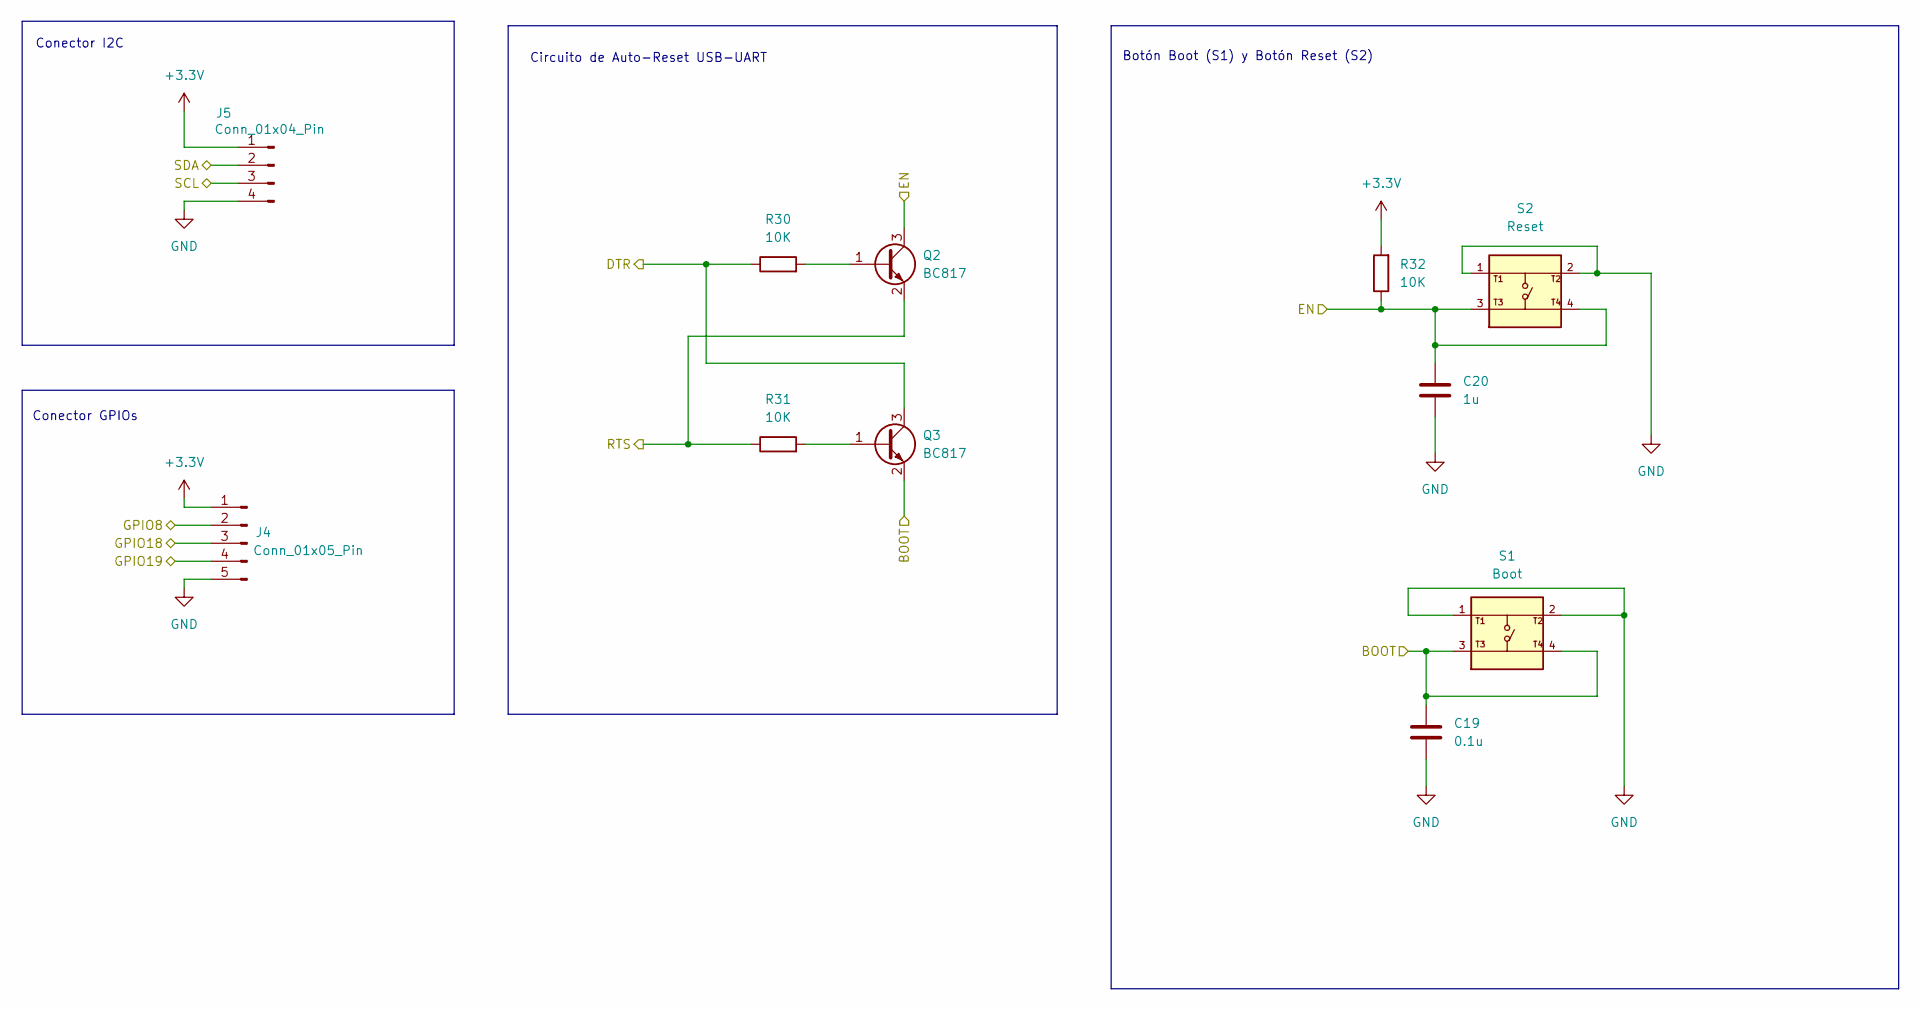
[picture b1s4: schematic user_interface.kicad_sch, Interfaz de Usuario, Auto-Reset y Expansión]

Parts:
C19: 0.1u; C_0805_2012Metric
C20: 1u; C_0805_2012Metric
J4: Conn_01x05_Pin; PinHeader_1x05_P2.54mm_Vertical
J5: Conn_01x04_Pin; PinHeader_1x04_P2.54mm_Vertical
Q2, Q3: BC817; SOT-23
R30, R31, R32: 10K; R_0805_2012Metric
S1: Boot; SW_USLPT2819DT2TR; PARTREV P
S2: Reset; SW_USLPT2819DT2TR; PARTREV P

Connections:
+3.3V: J4.1, J5.1, R32.2; also elsewhere on the board
/ESP32-C3-02/BOOT: C19.1, Q3.2 (E), S1.3, S1.4; also elsewhere on the board
/ESP32-C3-02/DTR: Q3.3 (C), R30.1; also elsewhere on the board
/ESP32-C3-02/EN: C20.1, Q2.3 (C), R32.1, S2.3, S2.4; also elsewhere on the board
/ESP32-C3-02/GPIO8: J4.2; also elsewhere on the board
/ESP32-C3-02/GPIO18: J4.3; also elsewhere on the board
/ESP32-C3-02/GPIO19: J4.4; also elsewhere on the board
/ESP32-C3-02/RTS: Q2.2 (E), R31.1; also elsewhere on the board
/ESP32-C3-02/SCL: J5.3; also elsewhere on the board
/ESP32-C3-02/SDA: J5.2; also elsewhere on the board
GND: C19.2, C20.2, J4.5, J5.4, S1.1, S1.2, S2.1, S2.2; also elsewhere on the board
unnamed: Q2.1 (B), R30.2
unnamed: Q3.1 (B), R31.2

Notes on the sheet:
Botón Boot (S1) y Botón Reset (S2)
Conector I2C
Circuito de Auto-Reset USB-UART
Conector GPIOs

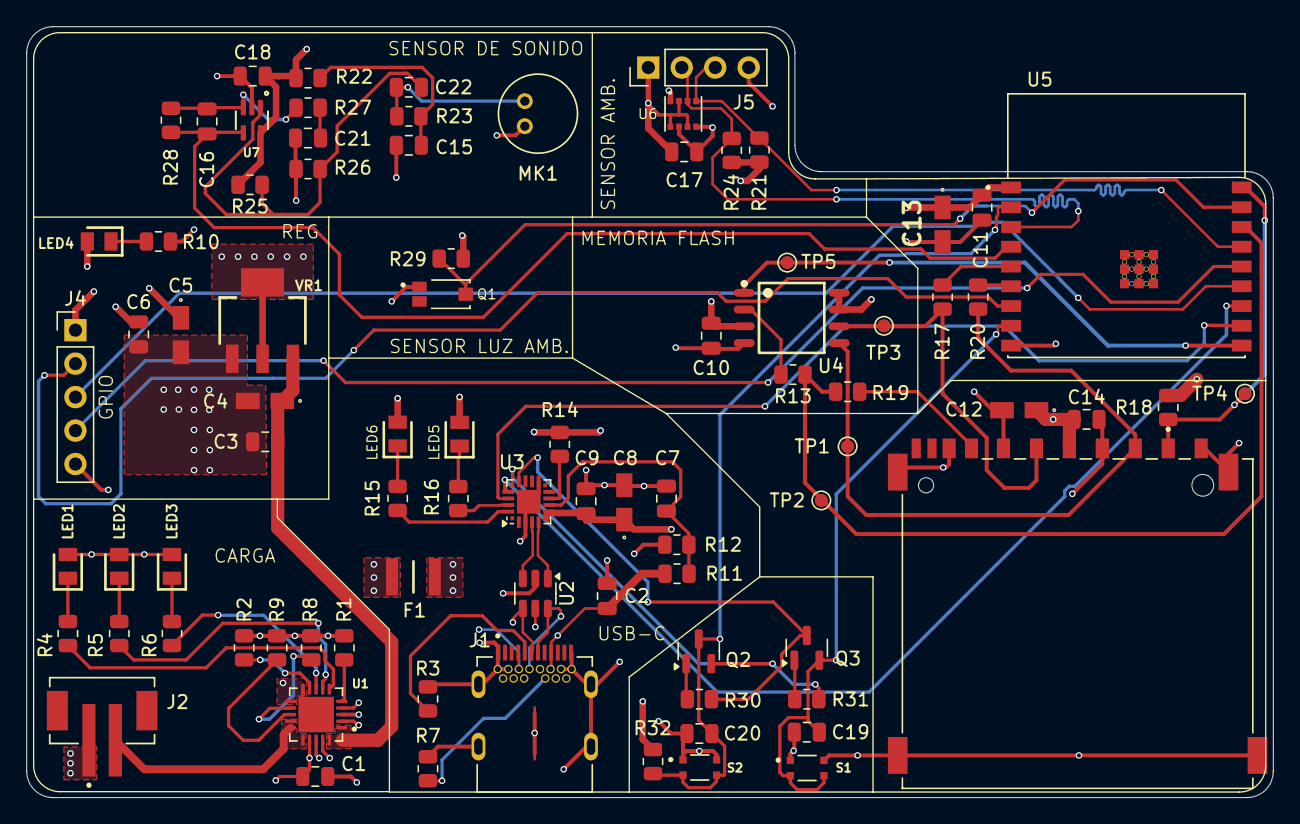
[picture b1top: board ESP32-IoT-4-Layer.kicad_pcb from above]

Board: 4 copper layers, 94.6 x 58.5 mm, 85 parts (0 on the bottom side), 58 nets.

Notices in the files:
README.md:
8. Licencia y Uso:
Este diseño de hardware se distribuye bajo la licencia **CERN Open Hardware Licence Version 2 - Weakly Reciprocal (CERN-OHL-W)** o **MIT License** para propósitos educativos y de desarrollo. Los esquemáticos, diagramas y archivos de fabricación son de libre consulta y adaptación citando la fuente original.
